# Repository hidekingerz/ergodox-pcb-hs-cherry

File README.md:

# ergodox-pcb-hs-cherry

Holtite Socket対応版Ergodox PCBデータです。  
以下のリポジトリを元に変更しています。

https://github.com/bishboria/ErgoDox

[Build-Logはこちら](https://gist.github.com/hidekingerz/674485b1bc5f276b9785774917839918)です。

# はじめに
はんだ付け無しでキースイッチとTeensy2を設置できる基板です。
IOエキスパンダと各種抵抗、I/Fは対応していません。

なお、実際に組み立てて動作するところは確認していますが、LEDは趣味ではないのでLED点灯のみ動作確認をしていません。

## 対応Holtite Socket
以下のどちらかに対応しています。

- [8134-HC-8P2](http://www.te.com/jpn-ja/product-7-1437514-0.html)  
- [8134-HC-8P3](http://www.te.com/jpn-ja/product-7-1437514-1.html)

## 必要な部品
|パーツ|リンク|量|
|:---|:---|:---|
|PCB|	-	|2|
|Teensy USB Board, Version 2.0|http://www.pjrc.com |1|
|MCP23018 I/O expander|Digikey: MCP23018-E/SP-ND|1|
|3.5mm TRRS connector|Digikey: CP-43514-ND|2|
|USB mini B connector|Digikey: WM17115-ND|1|
|USB mini B plug|Digikey: H2955-ND|1|
|0.1 UF ceramic capacitor|Digikey: BC2665CT-ND*|1|
|1N4148 diode   (SOD-123 package (SMD), or DO-35 (through hole 0.3" pitch))|Digikey: 1N4148FS-ND* or Digikey: 1N4148W-FDICT-ND*	|76-80|
|2.2K Ω resistor|Digikey: 2.2KQTR-ND*|2|
|3mm T1 LED|Digikey: 160-1034-ND*| |
|220 Ω resistor (match to led)	|Digikey: 220QBK-ND*|3|
|Cherry MX switch|Mouser: MX1A-*****|76-80|
|USB cable Male A to male mini B|USBFirewire: www.usbfirewire.com*|	1|
|TRRS cable	|MyCableMart: www.mycablemart.com*|1|
|holtite|Digikey:A114359-ND or A114358-ND| (152-160) + 24|

## PCBの入手方法
ご自身でGerberファイルを生成し、PCBGOGO等の基盤制作業者にご依頼ください。

# 実装

組み立て方法は通常のErgodoxと変わりません。HoltiteSocketをスルーホールに圧着するところが通常版との違いになります。

## Holtite socketの圧着方法
下記動画を参考にしてください。

## 取付時の注意点
以下を参照

### IOエキスパンダははんだ付けする
IOエキスパンダを取り付けるスルーホールはHoltiteSocket適合サイズに変更していますが、IOエキスパンダの脚が細すぎて適合しません。

HoltiteSocketは利用せず、通常通り半田付けしてください。

### Falbatechのアクリルキースイッチプレートを利用した場合の適合表

Falbatechのアクリルケースについているスイッチプレートを使用した場合、厚みによりMX互換品のキースイッチでも高さが足りずに接触できない種類のものが有りました。
メタルのスイッチプレートを利用している方はどのスイッチでも使えると思います。

|メーカー|種類|結果|
|:---|:---|:---|
|CheeryMX|黒軸|OK|
||青軸|OK|
||赤軸|OK|
|ZealPC|R9 Purple Zealio Switches|OK|
|Kaihua|Kailh Speed Switches|NG|

# Special Thanks
[haru-akeさんの HoltiteSocket対応版Let'sSplit](https://github.com/haru-ake/lets-split-pcb-hs-cherry)のPCBを頂いたことから本プロジェクトが始まりました。

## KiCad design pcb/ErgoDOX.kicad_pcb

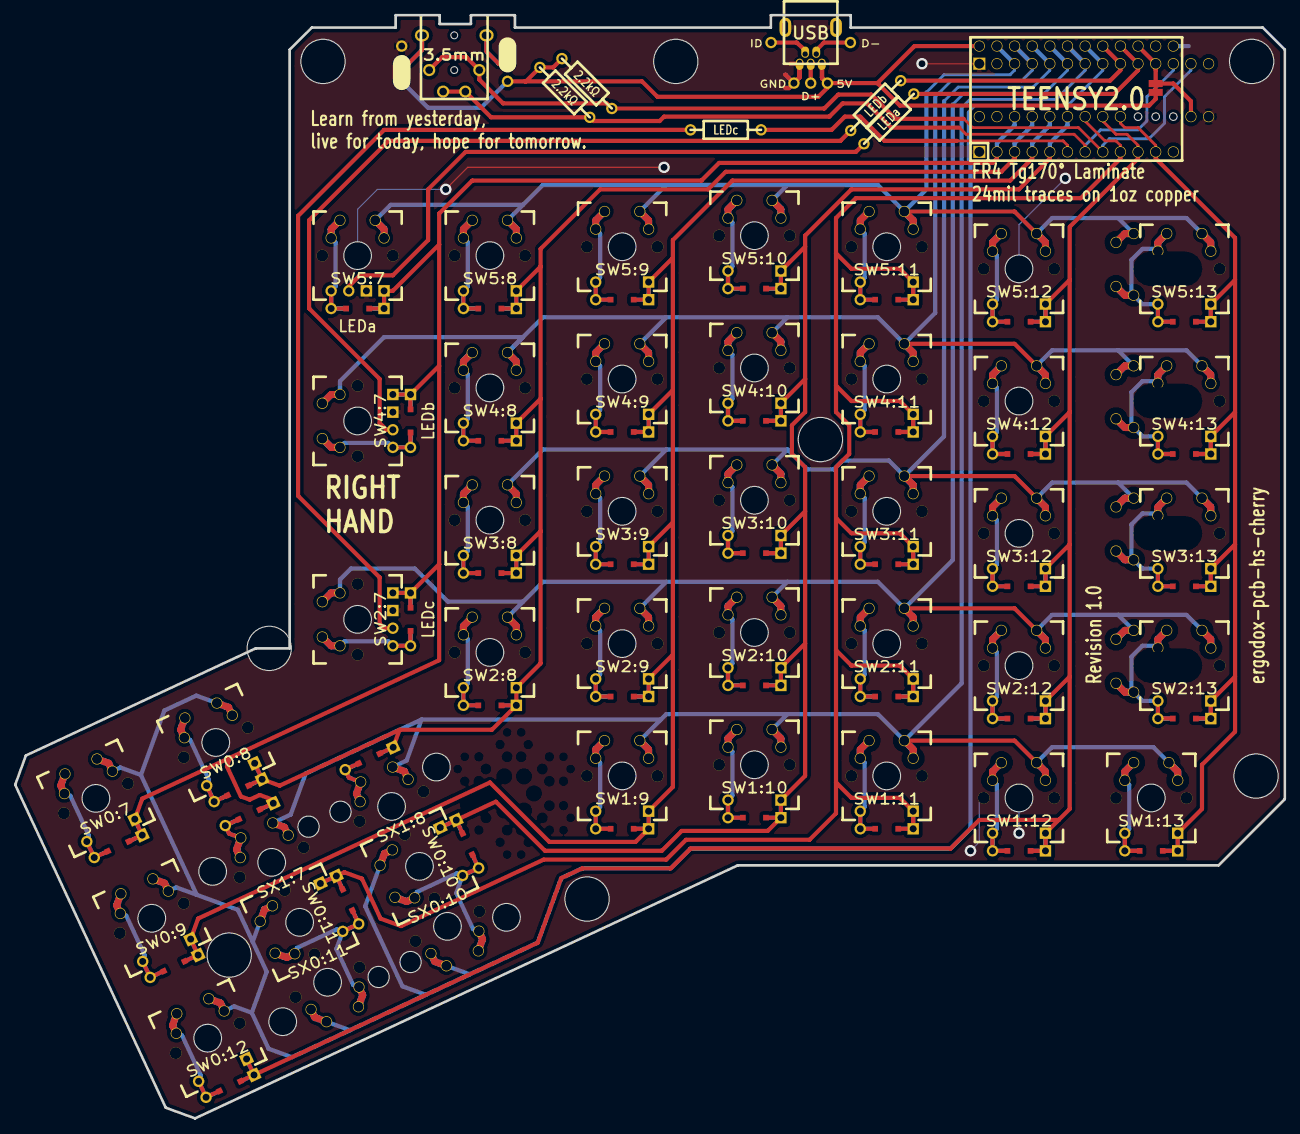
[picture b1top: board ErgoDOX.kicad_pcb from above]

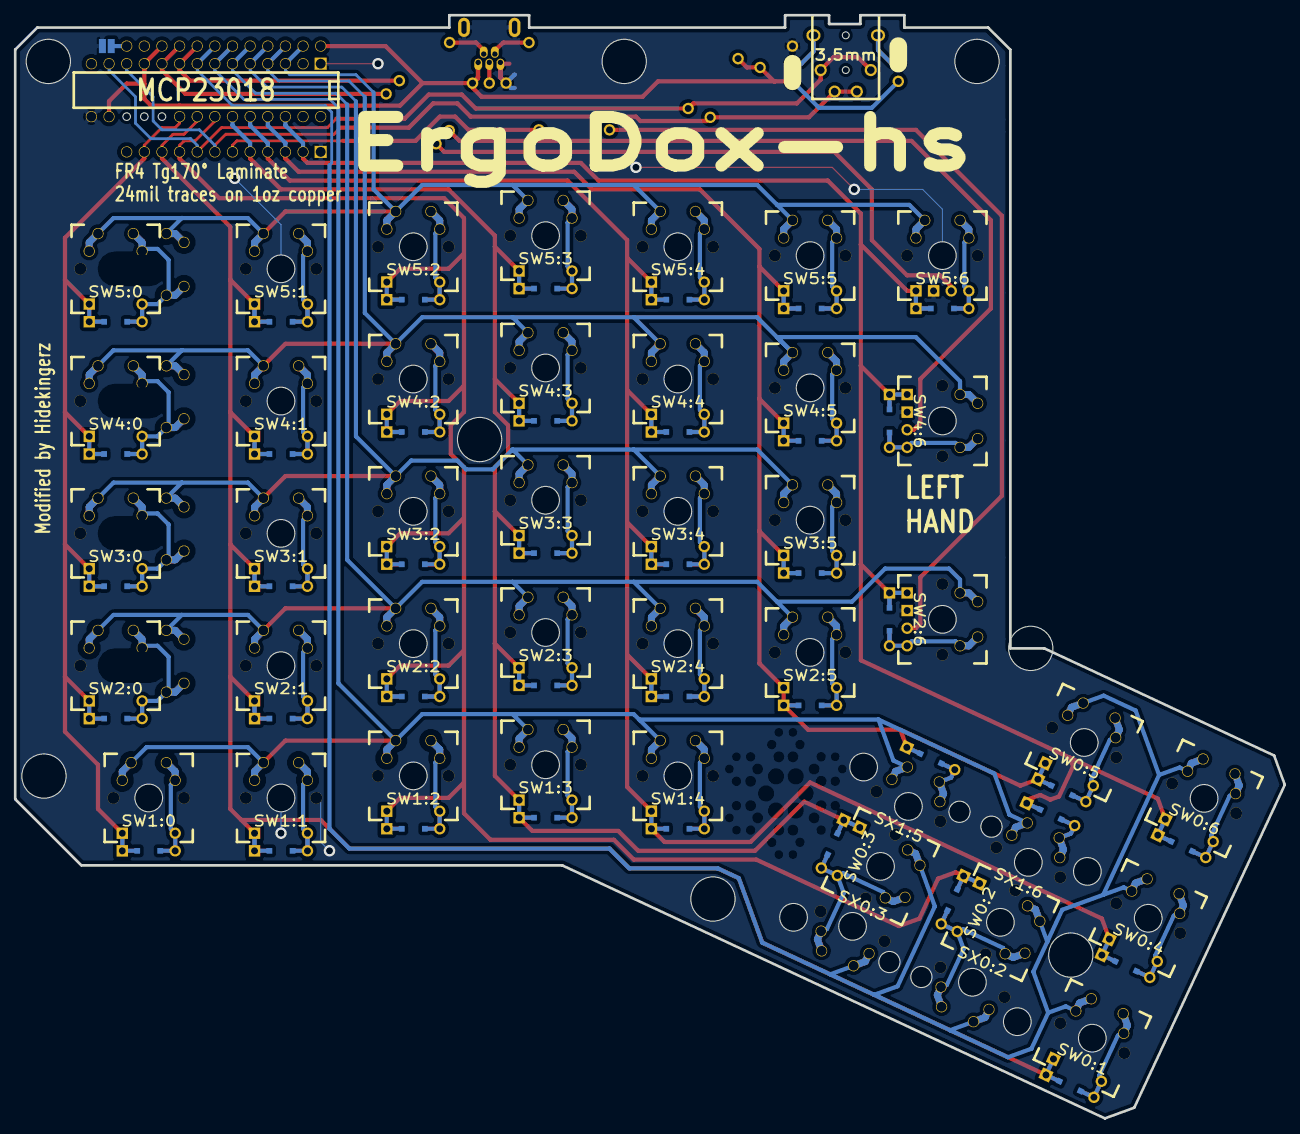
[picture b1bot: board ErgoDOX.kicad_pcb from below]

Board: 2 copper layers, 182.8 x 158.9 mm, 63 parts (3 on the bottom side), 65 nets.

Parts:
D1:7, D1:8: D; DIODE
H99: MECHANICAL; ErgoDOXmech
J1: USB; USBMINImod
J2: 3.5mm; 4pin35mmAudio
J3, J4: JMP; 100PITCH1X3
JP1, JP2: JUMPER; GAP
LED_A1: LEDa; MX_LED
LED_B1: LEDb; MX_LED
LED_C1: LEDc; MX_LED
R1, R2: 2.2kΩ; RESISTOR
RA1: LEDa; RESISTOR
RB1: LEDb; RESISTOR
RC1: LEDc; RESISTOR
S1, S2: STAB200; STAB_PCB940
SW0:7: SW0:6; MX_FLIP_DIODE
SW0:8: SW0:5; MX_FLIP_DIODE
SW0:9: SW0:4; MX_FLIP_DIODE
SW0:10: SW0:3; MX_FLIP_DIODE
SW0:11: SW0:2; MX_FLIP_DIODE
SW0:12: SW0:1; MX_FLIP_DIODE
SW1:9: SW1:4; MX_FLIP_DIODE
SW1:10: SW1:3; MX_FLIP_DIODE
SW1:11: SW1:2; MX_FLIP_DIODE
SW1:12: SW1:1; MX_FLIP_DIODE
SW1:13: SW1:0; MX_FLIP_DIODE
SW2:7: SW2:6; MX_FLIP_DIODE
SW2:8: SW2:5; MX_FLIP_DIODE
SW2:9: SW2:4; MX_FLIP_DIODE
SW2:10: SW2:3; MX_FLIP_DIODE
SW2:11: SW2:2; MX_FLIP_DIODE
SW2:12: SW2:1; MX_FLIP_DIODE
SW2:13: SW2:0; MX_FLIP_XX
SW3:8: SW3:5; MX_FLIP_DIODE
SW3:9: SW3:4; MX_FLIP_DIODE
SW3:10: SW3:3; MX_FLIP_DIODE
SW3:11: SW3:2; MX_FLIP_DIODE
SW3:12: SW3:1; MX_FLIP_DIODE
SW3:13: SW3:0; MX_FLIP_XX
SW4:7: SW4:6; MX_FLIP_DIODE
SW4:8: SW4:5; MX_FLIP_DIODE
SW4:9: SW4:4; MX_FLIP_DIODE
SW4:10: SW4:3; MX_FLIP_DIODE
SW4:11: SW4:2; MX_FLIP_DIODE
SW4:12: SW4:1; MX_FLIP_DIODE
SW4:13: SW4:0; MX_FLIP_XX
SW5:7: SW5:6; MX_FLIP_DIODE
SW5:8: SW5:5; MX_FLIP_DIODE
SW5:9: SW5:4; MX_FLIP_DIODE
SW5:10: SW5:3; MX_FLIP_DIODE
SW5:11: SW5:2; MX_FLIP_DIODE
SW5:12: SW5:1; MX_FLIP_DIODE
SW5:13: SW5:0; MX_FLIP_XX
SX0:10: SX0:3; MX_FLIP
SX0:11: SX0:2; MX_FLIP
SX1:7: SX1:6; MX_FLIP
SX1:8: SX1:5; MX_FLIP
U1: TEENSY2.0; TEENSY_2.0
U2: MCP23018; DIP28_300

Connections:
/COL0: SW1:13.4, SW2:13.4, SW3:13.4, SW4:13.4, SW5:13.4, U1.11, U2.20
/COL1: SW0:12.4, SW1:12.4, SW2:12.4, SW3:12.4, SW4:12.4, SW5:12.4, U1.10, U2.21
/COL4: SW0:9.4, SW1:9.4, SW2:9.4, SW3:9.4, SW4:9.4, SW5:9.4, U1.4, U2.24
/COL5: D1:8.2, SW0:8.4, SW2:8.4, SW3:8.4, SW4:8.4, SW5:8.4, U1.3, U2.25
/COL6: D1:7.2, SW0:7.4, SW2:7.4, SW4:7.4, SW5:7.4, U1.2, U2.26
/COL10: SW0:10.4, SW1:10.4, SW2:10.4, SW3:10.4, SW4:10.4, SW5:10.4, U1.5, U2.23
/COL11: SW0:11.4, SW1:11.4, SW2:11.4, SW3:11.4, SW4:11.4, SW5:11.4, U1.9, U2.22
/LED_A: RA1.1, U1.21
/LED_B: RB1.1, U1.22
/LED_C: RC1.1, U1.6
/ROW0: SW0:7.1, SW0:8.1, SW0:9.1, SW0:10.1, SW0:11.1, SW0:12.1, SX0:10.1, SX0:11.1, U1.23, U2.8
/ROW1: SW1:9.1, SW1:10.1, SW1:11.1, SW1:12.1, SW1:13.1, SX1:7.1, SX1:8.1, U1.24, U2.7
/ROW2: SW2:7.1, SW2:8.1, SW2:9.1, SW2:10.1, SW2:11.1, SW2:12.1, SW2:13.1, U1.25, U2.6
/ROW3: SW3:8.1, SW3:9.1, SW3:10.1, SW3:11.1, SW3:12.1, SW3:13.1, U1.26, U2.5
/ROW4: SW4:7.1, SW4:8.1, SW4:9.1, SW4:10.1, SW4:11.1, SW4:12.1, SW4:13.1, U1.27, U2.4
/ROW5: SW5:7.1, SW5:8.1, SW5:9.1, SW5:10.1, SW5:11.1, SW5:12.1, SW5:13.1, U1.28, U2.3
/SCLM: J2.3, J2.5, R2.2, U1.7, U2.12
/SDAM: J2.2, J2.6, R1.2, U1.8, U2.13
GND: H99.0, J1.5, J1.6, J3.3, J4.3, JP2.1, LED_A1.2, LED_B1.2, LED_C1.2, S1.0, S2.0, SW0:7.0, SW0:8.0, SW0:9.0, SW0:10.0, SW0:11.0, SW0:12.0, SW1:9.0, SW1:10.0, SW1:11.0, SW1:12.0, SW1:13.0, SW2:7.0, SW2:8.0, SW2:9.0, SW2:10.0, SW2:11.0, SW2:12.0, SW2:13.0, SW3:8.0, SW3:9.0, SW3:10.0, SW3:11.0, SW3:12.0, SW3:13.0, SW4:7.0, SW4:8.0, SW4:9.0, SW4:10.0, SW4:11.0, SW4:12.0, SW4:13.0, SW5:7.0, SW5:8.0, SW5:9.0, SW5:10.0, SW5:11.0, SW5:12.0, SW5:13.0, SX0:10.0, SX0:11.0, SX1:7.0, SX1:8.0, U1.1, U1.18, U2.1, U2.15
unnamed: J2.4, J4.2
unnamed: J2.1, J3.2
unnamed: SW5:12.2, SW5:12.3
unnamed: SW5:8.2, SW5:8.3
unnamed: SW5:7.2, SW5:7.3
unnamed: D1:8.1, SX1:8.2
unnamed: SW5:9.2, SW5:9.3
unnamed: SW5:10.2, SW5:10.3
unnamed: SW5:11.2, SW5:11.3
unnamed: SW1:9.2, SW1:9.3
unnamed: SW0:10.2, SW0:10.3, SX0:10.2
unnamed: D1:7.1, SX1:7.2
unnamed: SW2:10.2, SW2:10.3
unnamed: SW3:9.2, SW3:9.3
unnamed: SW3:8.2, SW3:8.3
unnamed: SW2:7.2, SW2:7.3
unnamed: SW2:8.2, SW2:8.3
unnamed: SW2:9.2, SW2:9.3
unnamed: SW2:11.2, SW2:11.3
unnamed: SW1:11.2, SW1:11.3
unnamed: SW1:10.2, SW1:10.3
unnamed: SW2:12.2, SW2:12.3
unnamed: SW5:13.2, SW5:13.3
unnamed: SW4:9.2, SW4:9.3
unnamed: SW4:11.2, SW4:11.3
unnamed: SW4:12.2, SW4:12.3
unnamed: SW2:13.2, SW2:13.3
unnamed: SW4:13.2, SW4:13.3
unnamed: SW3:13.2, SW3:13.3
unnamed: SW3:12.2, SW3:12.3
unnamed: SW3:11.2, SW3:11.3
unnamed: SW3:10.2, SW3:10.3
unnamed: SW0:8.2, SW0:8.3
unnamed: SW1:13.2, SW1:13.3
unnamed: SW1:12.2, SW1:12.3
unnamed: SW0:12.2, SW0:12.3
unnamed: SW0:9.2, SW0:9.3
unnamed: SW0:7.2, SW0:7.3
unnamed: SW4:7.2, SW4:7.3
unnamed: SW4:8.2, SW4:8.3
unnamed: SW4:10.2, SW4:10.3
unnamed: LED_C1.1, RC1.2
unnamed: LED_B1.1, RB1.2
unnamed: LED_A1.1, RA1.2
unnamed: SW0:11.2, SW0:11.3, SX0:11.2
VCC: J1.1, J3.1, J4.1, JP1.1, R1.1, R2.1, U1.20, U1.29, U2.11, U2.16

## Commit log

2018-01-10 add data
    kicad data
2018-01-10 rm file
    不必要なガーバーファイルを削除。
2018-01-12 修正
    Gerberファイルを削除。
    Teensy2とIOエキスパンダもソケット対応。
2018-01-13 ファイル整理
    garberファイルを削除
2018-01-13 mod README
    READMEを修正
2018-01-15 mod README.md
2018-01-28 Update LICENSE
2018-01-28 add image
    イメージを追加
    後でちゃんとしたカメラで撮る。
2018-01-28 README ファイルの微修正
    テーブル等々を修正
2018-01-28 HoltiteSockeのDigikeyの品番を追記
    追記した
2018-01-28 add SpecialThanks
    haru-akeさんの事を追記
2018-01-28 完成版の写真を追加
    add pic
2018-02-01 ビルドログを追加
    ・タイトルタイポを修正
    ・ビルドログを追加
